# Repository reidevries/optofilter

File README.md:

# optofilter
This is a sallen-key filter with optocouplers instead of fixed resisters, allowing CV control. It is unique because inputs for three filter responses which are mixed at the output. It could use some clipping diodes to stop the resonance from clipping the op-amps, and using two PCBs is really totally unnecessary, I just thought it would be nifty to have one PCB contain the LEDs for the optocoupler and the other PCB contain the LDRs.

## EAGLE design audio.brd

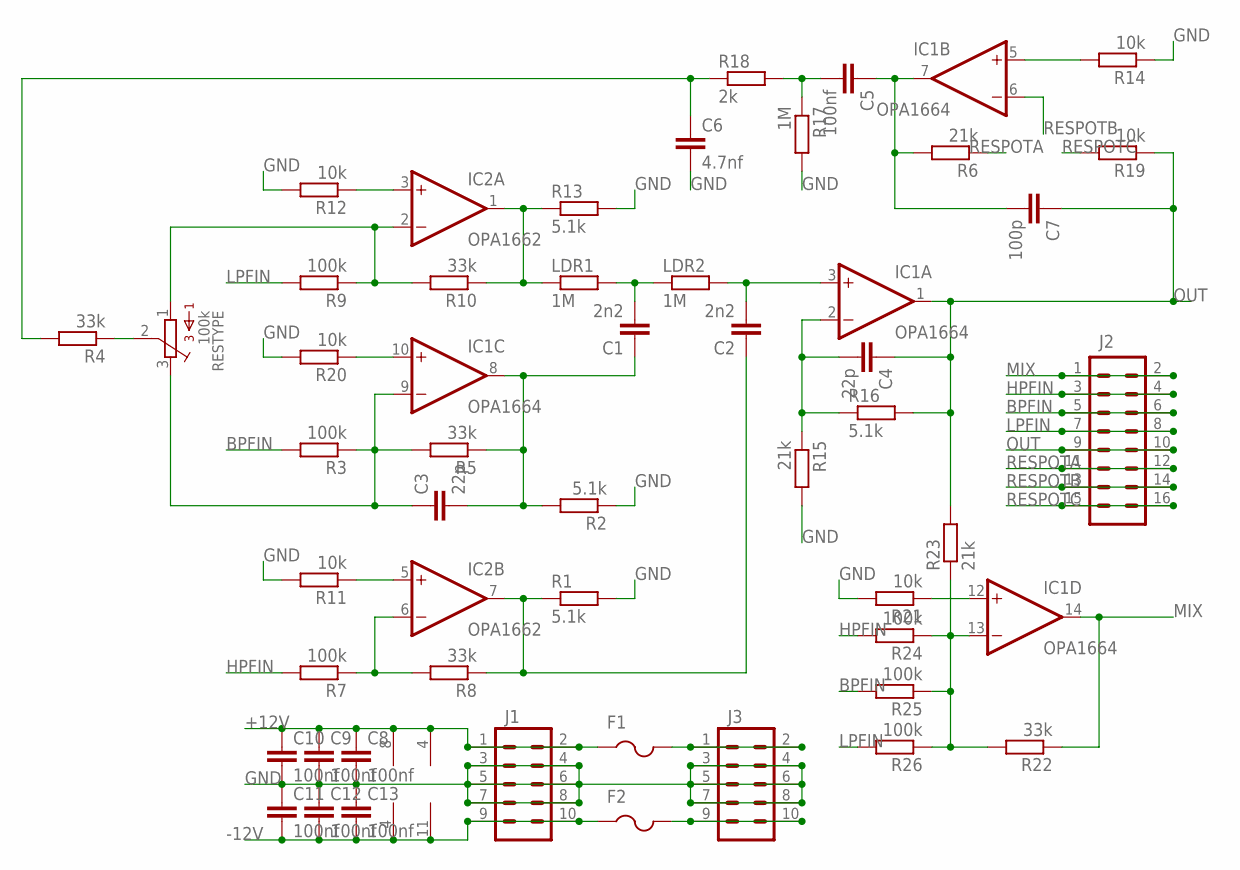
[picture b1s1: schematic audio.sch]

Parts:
C1, C2: 2n2; C050-025X075
C3, C4: 22p; C1206
C5, C8, C9, C10, C11, C12, C13: 100nf; C1206
C6: 4.7nf; C1206
C7: 100p; C1206
F1, F2: PTCFUSE-1206; R1206
IC1: OPA1664; SO14
IC2: OPA1662; SO08
J1, J3: M05X2PTH; AVR_ICSP
J2: M08X2; 2X8
LDR1, LDR2: 1M; 0411V
R1, R2, R13, R16: 5.1k; R1206
R3, R7, R9, R24, R25, R26: 100k; R1206
R4, R5, R8, R10, R22: 33k; R1206
R6, R15, R23: 21k; R1206
R11, R12, R14, R19, R20, R21: 10k; R1206
R17: 1M; R1206
R18: 2k; R1206
RESTYPE: 100k; 3386C

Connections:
+12V: C8.1, C9.1, C10.1, F1.1, IC1.4 (V+), IC2.8 (V+), J1.1, J1.2
-12V: C11.2, C12.2, C13.2, F2.1, IC1.11 (V-), IC2.4 (V-), J1.9, J1.10
BPFIN: J2.5, J2.6, R3.2, R25.2
GND: C6.2, C8.2, C9.2, C10.2, C11.1, C12.1, C13.1, J1.3, J1.4, J1.5, J1.6, J1.7, J1.8, J3.3, J3.4, J3.5, J3.6, J3.7, J3.8, R1.2, R2.1, R11.2, R12.2, R13.2, R14.1, R15.2, R17.2, R20.2, R21.2
HPFIN: J2.3, J2.4, R7.2, R24.2
LPFIN: J2.7, J2.8, R9.2, R26.2
MIX: IC1.14 (OUT), J2.1, J2.2, R22.1
unnamed: IC1.10 (+IN), R20.1
unnamed: C4.2, IC1.2 (-IN), R15.1, R16.1
unnamed: C1.1, C3.2, IC1.8 (OUT), R2.2, R5.1
unnamed: R4.1, RESTYPE.2
unnamed: IC1.5 (+IN), R14.2
unnamed: C2.2, IC1.3 (+IN), LDR2.2
unnamed: C1.2, LDR1.2, LDR2.1
unnamed: F2.2, J3.9, J3.10
unnamed: C3.1, IC1.9 (-IN), R3.1, R5.2, RESTYPE.3
unnamed: F1.2, J3.1, J3.2
unnamed: IC2.6 (-IN), R7.1, R8.2
unnamed: C2.1, IC2.7 (OUT), R1.1, R8.1
unnamed: IC2.5 (+IN), R11.1
unnamed: IC2.2 (-IN), R9.1, R10.2, RESTYPE.1
unnamed: IC2.3 (+IN), R12.1
unnamed: IC2.1 (OUT), LDR1.1, R10.1, R13.1
unnamed: C5.1, C7.2, IC1.7 (OUT), R6.2
unnamed: C5.2, R17.1, R18.2
unnamed: C6.1, R4.2, R18.1
unnamed: IC1.12 (+IN), R21.1
unnamed: IC1.13 (-IN), R22.2, R23.1, R24.1, R25.1, R26.1
OUT: C4.1, C7.1, IC1.1 (OUT), J2.9, J2.10, R16.2, R19.1, R23.2
RESPOTA: J2.11, J2.12, R6.1
RESPOTB: IC1.6 (-IN), J2.13, J2.14
RESPOTC: J2.15, J2.16, R19.2

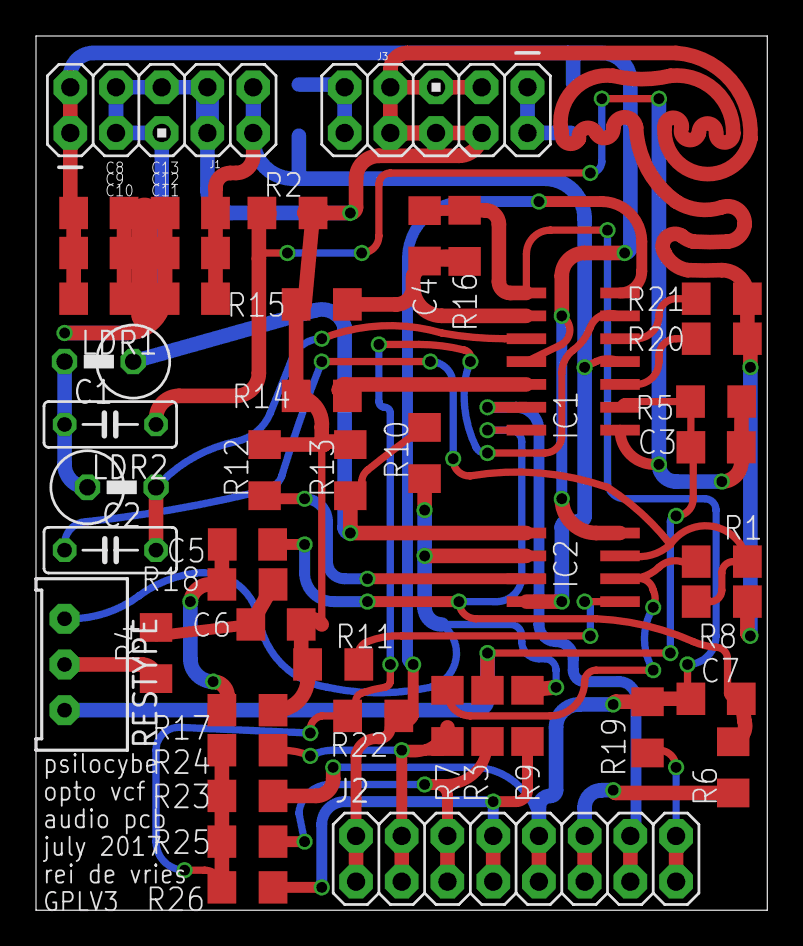
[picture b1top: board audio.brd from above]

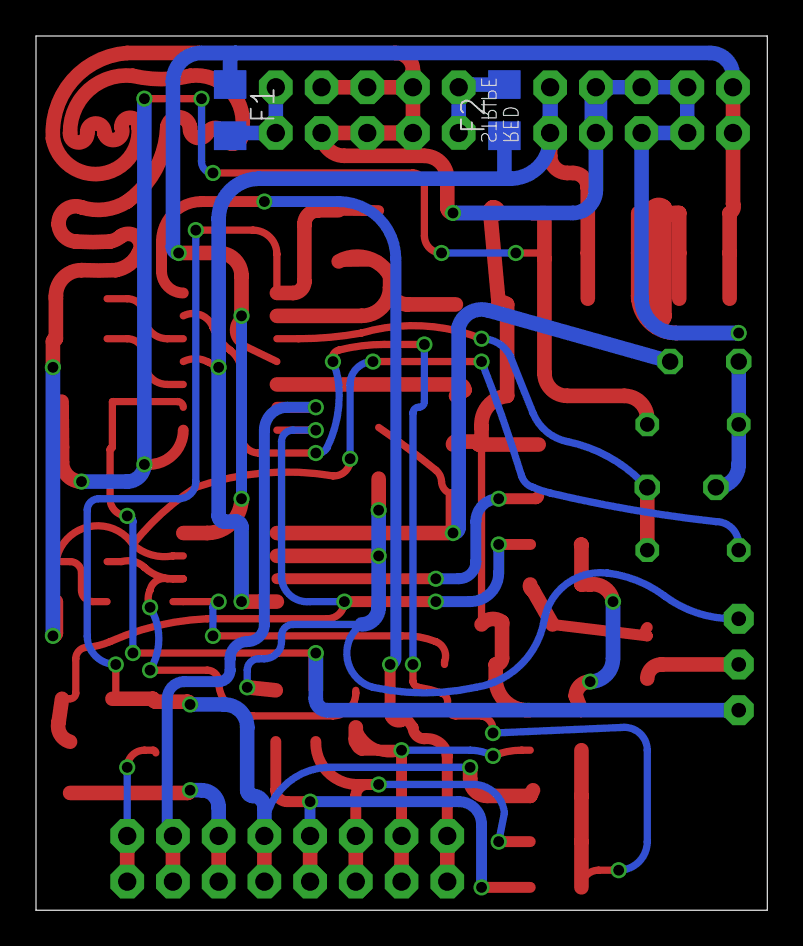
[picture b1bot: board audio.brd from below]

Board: 2 copper layers, 40.6 x 48.6 mm, 49 parts (2 on the bottom side), 32 nets.

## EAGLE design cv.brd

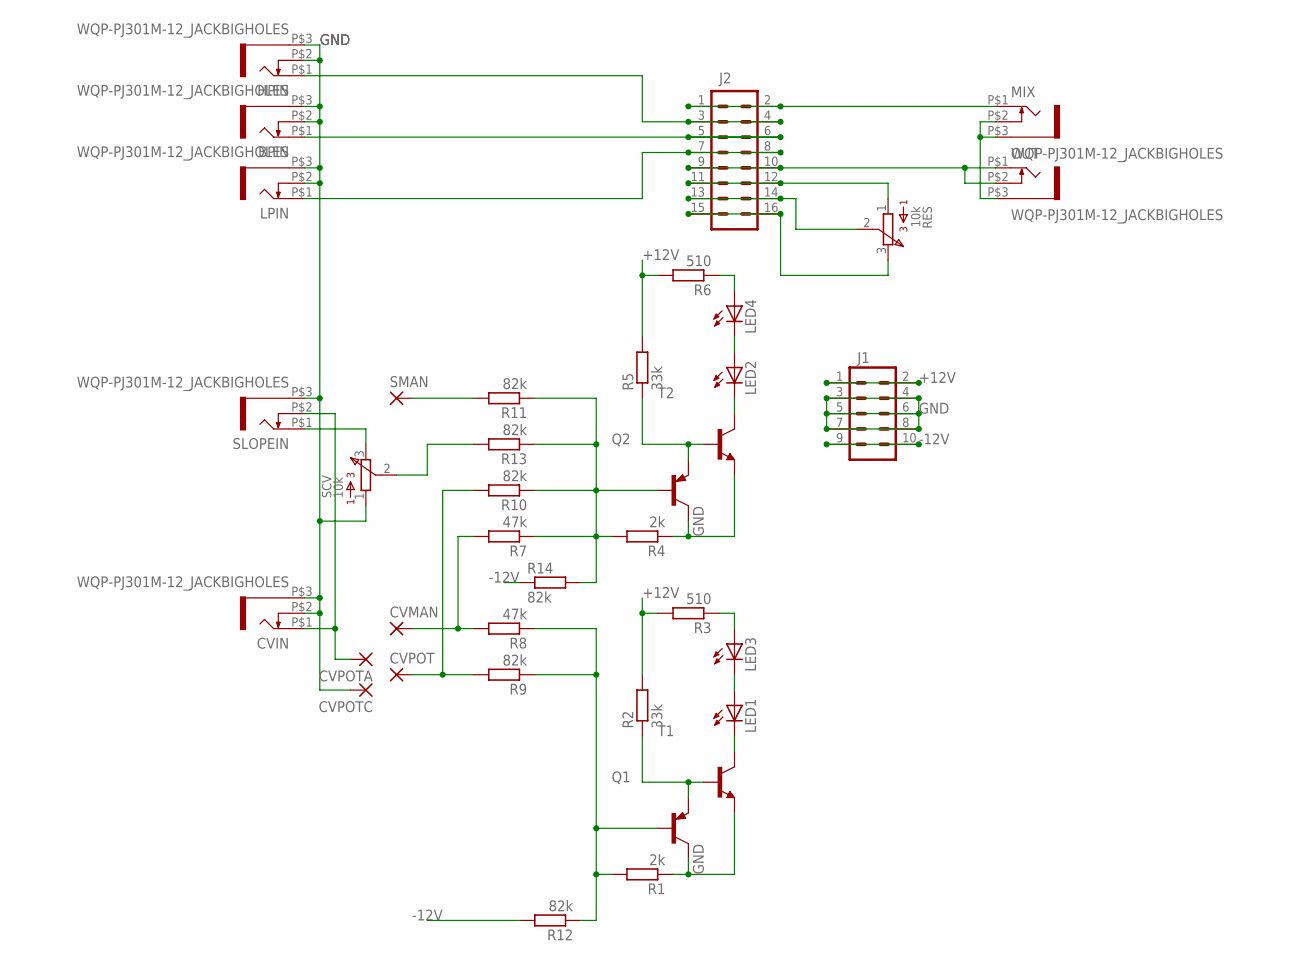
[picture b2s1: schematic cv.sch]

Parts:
BPIN: WQP-PJ301M-12_JACKBIGHOLES; WQP-PJ301M-12_JACK
CVIN: WQP-PJ301M-12_JACKBIGHOLES; WQP-PJ301M-12_JACK
CVMAN: 2,0/0,9-S
CVPOT: 2,0/0,9-S
CVPOTA: 2,0/0,9-S
CVPOTC: 2,0/0,9-S
HPIN: WQP-PJ301M-12_JACKBIGHOLES; WQP-PJ301M-12_JACK
J1: M05X2PTH; AVR_ICSP
J2: M08X2; 2X8
LED1, LED2: LEDCHIP-LED0805; CHIP-LED0805
LED3, LED4: LED5MM
LPIN: WQP-PJ301M-12_JACKBIGHOLES; WQP-PJ301M-12_JACK
MIX: WQP-PJ301M-12_JACKBIGHOLES; WQP-PJ301M-12_JACK
OUT: WQP-PJ301M-12_JACKBIGHOLES; WQP-PJ301M-12_JACK
Q1, Q2: MMBT3906LT1-PNP-SOT23-BEC; SOT23-BEC
R1, R4: 2k; R1206
R2, R5: 33k; R1206
R3, R6: 510; R1206
R7, R8: 47k; R1206
R9, R10, R11, R12, R13, R14: 82k; R1206
RES: 10k; 91
SCV: 10k; 91
SLOPEIN: WQP-PJ301M-12_JACKBIGHOLES; WQP-PJ301M-12_JACK
SMAN: 2,0/0,9-S
T1, T2: MMBT3904LT1-NPN-SOT23-BEC; SOT23-BEC

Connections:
+12V: J1.1, J1.2, R2.2, R3.2, R5.2, R6.2
-12V: J1.9, J1.10, R12.2, R14.1
GND: BPIN.P$2 (3), BPIN.P$3 (1), CVIN.P$2 (3), CVIN.P$3 (1), CVPOTC.1, HPIN.P$2 (3), HPIN.P$3 (1), J1.3, J1.4, J1.5, J1.6, J1.7, J1.8, LPIN.P$2 (3), LPIN.P$3 (1), MIX.P$2 (3), MIX.P$3 (1), OUT.P$3 (1), Q1.C, Q2.C, R1.1, R4.1, SCV.1, SLOPEIN.P$3 (1), T1.E, T2.E
unnamed: J2.1, J2.2, MIX.P$1 (2)
unnamed: J2.7, J2.8, LPIN.P$1 (2)
unnamed: J2.9, J2.10, OUT.P$1 (2), OUT.P$2 (3)
unnamed: CVIN.P$1 (2), CVPOTA.1, SLOPEIN.P$2 (3)
unnamed: SCV.3, SLOPEIN.P$1 (2)
unnamed: BPIN.P$1 (2), J2.5, J2.6
unnamed: LED3.A, R3.1
unnamed: R13.2, SCV.2
unnamed: CVPOT.1, R9.2, R10.2
unnamed: Q1.B, R1.2, R8.1, R9.1, R12.1
unnamed: R11.2, SMAN.1
unnamed: CVMAN.1, R7.2, R8.2
unnamed: Q1.E, R2.1, T1.B
unnamed: LED1.C, T1.C
unnamed: LED1.A, LED3.K (C)
unnamed: Q2.E, R5.1, T2.B
unnamed: HPIN.P$1 (2), J2.3, J2.4
unnamed: LED2.C, T2.C
unnamed: LED2.A, LED4.K (C)
unnamed: LED4.A, R6.1
unnamed: Q2.B, R4.2, R7.1, R10.1, R11.1, R13.1, R14.2
RESPOTA: J2.11, J2.12, RES.1
RESPOTB: J2.13, J2.14, RES.2
RESPOTC: J2.15, J2.16, RES.3

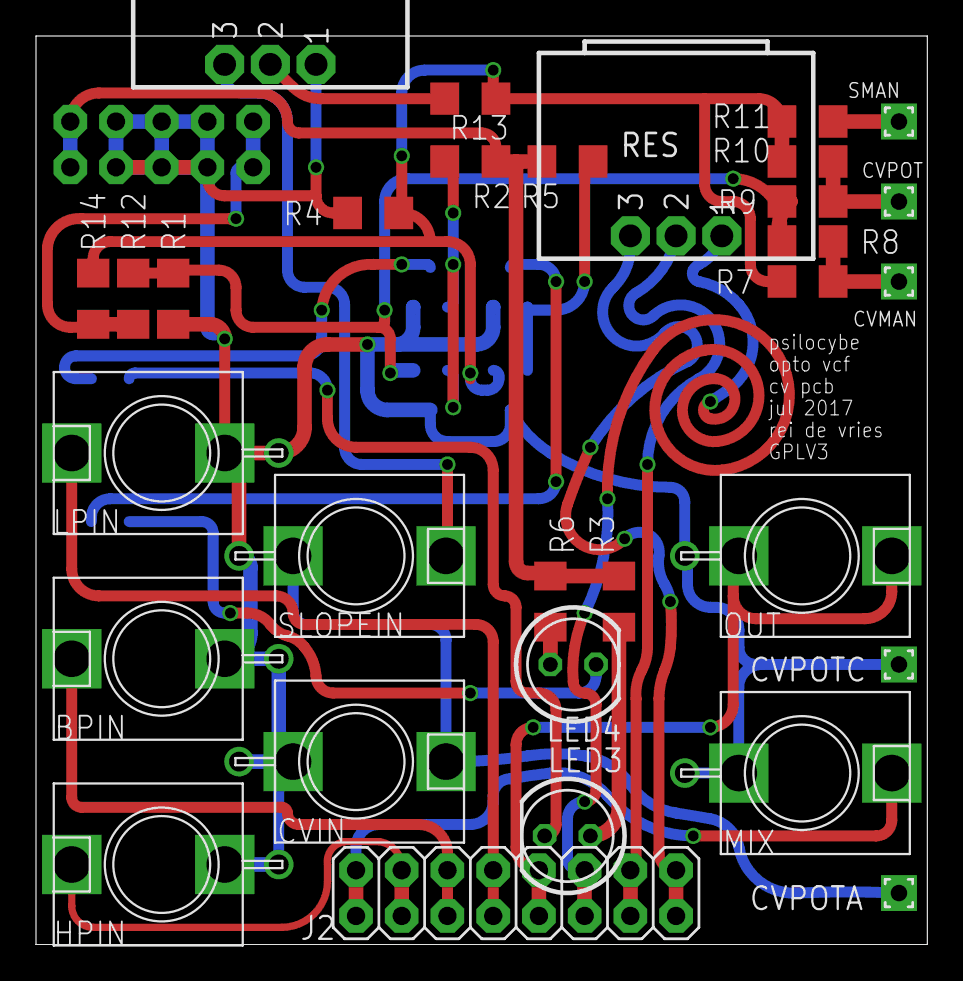
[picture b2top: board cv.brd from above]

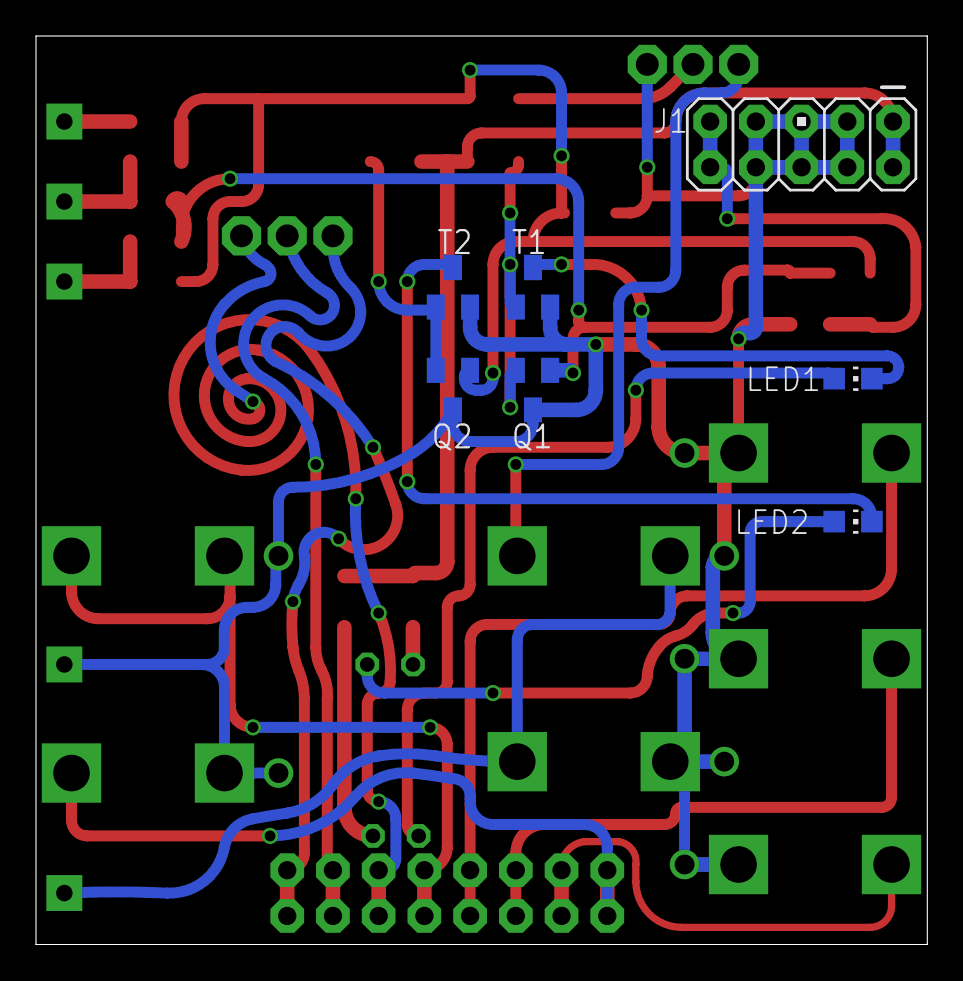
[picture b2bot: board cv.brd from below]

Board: 2 copper layers, 49.5 x 50.5 mm, 38 parts (7 on the bottom side), 27 nets.

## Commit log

2017-07-30 adds design files for v2
2017-07-30 Create LICENSE
2017-07-30 removed dumb mistake on audio board image and .brd file
2017-07-31 add info to readme
2017-07-31 typo fix

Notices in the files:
audio.brd:
GPLV3
parts and their libraries:
SparkFun-Connectors: Licensing: Creative Commons ShareAlike 4.0 International - https://creativecommons.org/licenses/by-sa/4.0
